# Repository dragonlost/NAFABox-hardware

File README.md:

# NAFABox-hardware   

__Version francaise :__    

Le but de ce projet, qui est née fin 2018, est de pouvoir proposer à tous des cartes électroniques plugables sur une carte Raspberry Pi (ou carte avec connecteur 40pins compatible) dédié aux astronomes amateurs.

Après 2 prototypes réalisés mais pas assez fonctionnel et compact à mon goût, l'idée fut de partir sur une achitecture modulaire stackable sur un Raspberry Pi.

Grâce à Kicad et ses possibilités 3D nous avons pu mener à bien ce projet.

Malheuresement, n'ayant pas de formation en électronique/design de PCB ou en réalisation mécanique, les réalisatons ne sont pas parfaite et ne respecte surement pas totalement les normes et caractéristique du domaine.

Ce projet est Open Source et donc j'invite toutes personnes voulant contribuer à sa réalisation à proposer un Pull Request/Issue ou à me contacter via mon Pseudo (le même que sur Github) sur Webastro ou sur le Discord : "Astro - FR".

__Attention :__ La plupart des modèles 3D présent dans de dossier __lib__ de chaque PCB sont issue du site https://grabcad.com/ et ne sont pas forcement tous OpenSource. Merci de respecter leurs droits de diffusion.

## Les différentes cartes :

Tout les schémas électronique sont disponible dans la Doc : https://github.com/dragonlost/NAFABox-hardware/tree/master/Doc/schema_pdf

### La carte de base :
(base_hat)     

Cette carte contient principalement 2 parties : 
- un composant DS3231 en I2C afin de pouvoir obtenir une base de temps permanente pour le Raspberry Pi ainsi qu'un logement de pile pour un CR2032 remplacable
- un connecteur et emplacement pour un ventillateur de 30x30mm controlé en PWM par le Raspberry PI.  

### La carte d'alimentation :
(alim_hat)    

Elle contient :
- Une entrée d'alimentation Jack DC protégé contre l'inversion de courant.
- 4 sorties :
	- protégées par des fusibles rearmable PPTC ( polyswitch/polyfuse) de 5A
	- mesurer en courant et tension à l'aide d'INA219 en I2C ( un par sortie)
	- de tension identique à la tension d'entrée
- un connecteur 8 broches avec la tension d'entré (x2) et la masse (x4) ainsi qu'une autre tension (VCC) entrée via le bornier prevue à cette effet
- un convertisseur DC-DC stepdown PDQE15-Q24-S5-D isolé ( désactivable) pouvant délivré 3A en 5V relié au pins 5v du Raspberry Pi.
- de pin permettant de couper/connecter chaque sortie via un Jumper ou des interupteurs externe ou via la carte relais.

### La carte Relais/ Focuser
(relais_hat)

Elle contient :
- Un système de 4 relais :
	- 4 relais piloté via les GPIO de carte Raspberry PI (GPIO 17, 18, 22 et 23)
	- 4 leds indiquant l'état des relais (dans le même ordre D1, D2, D3, D4)
	- 4 sorties par pins plugable sur la carte d'alimentation pour piloter les 4 sorties.
	- 4 bornier pour piloter un système externe
- un connecteur 8 broches avec la tension d'entrée (x2) et la masse (x4) ainsi qu'une autre tension (VCC) entrée via le bornier de la carte d'alimentation
- Un système pour piloter un moteur pas à pas afin de réaliser la mise au point.
	- un emplacemnt pour driveur moteur au format pololu
	- un connecteur DB9 au format RoboFocus (A1=1, A2=2, B1=3, B2=4, GND=5)
	- un système de 3 jumper afin de piloter l'état des pins (libre, 3.3v, GND)
	- pilotage via les GPIO (STEP=GPIO25, DIR=GPIO27, SLP=GPIO24)
	- l'alimentation 12v via la connecteur 8 pins.

### La carte Resistance chauffante et GPS
(res_hat)

Elle contient :
- un connecteur 8 broches avec la tension d'entrée (x2) et la masse (x4) ainsi qu'une autre tension (VCC) entrée via le bornier de la carte d'alimentation
- un connecteur 4 pins pour connecteur une carte GPS UART (3.3v-RX-TX-GND) :
	- 2 trous de fixation mécanique
	- 2 systèmes de jumper afin d'inverser le TX/RX ou sélectioner d'autre pin TX-RX pour la carte Nanopi-M4 
- une entrée Jack DC connecter a la tension VCC.
- un système de résistance chauffante piloter par I2C :
	- 2 résistance possible, connectable via 2x USB (résistance en 5V par exemple) ou via 2x RCA.
	- chaque sortie est mesurée en tension et courant via des INA219 comme la carte d'alimentation
	- un connecteur pour une carte BME280 en i2C afin de calculer le point de rosé via la température et l'humidité local.
	- 2 connecteurs pour 2 capteurs D18B20 1wire (pin7 du RPI) afin de mesurer la température des résistances.
	- Chaque résistance est pilotable en puissance via 2 mofset FDD844L-F085
	- Il est posible via un jumper de sélectionner la tension d'alimentation des résistances entre l'entrée Jack de la carte d'alimentation (nomé: 12V) et l'entrée jack de la carte résistance ou du bornier de la carte d'alimentation (nomé: VCC)

## Le Boitier :

Le boitier destiné à accueillir les différentes cartes a été concue comme les cartes afin d'être modulaire. Chaque carte possède donc sa propre pièce.    
Les modèles 3D des cartes sont aussi disponibles afin de permettre à chacun de réaliser son propre boitier.

Elle a été aussi concu afin d'être facilement imprimable sur des imprimantes de capacité d'impression de 20x20x20.    

Les pièces ont été dessiné sous CATIA par __SUPAII__ puis publié en format STEP afin que chacun puisse les modifiés/convertir avec n'importe quel logiciel de CAO.

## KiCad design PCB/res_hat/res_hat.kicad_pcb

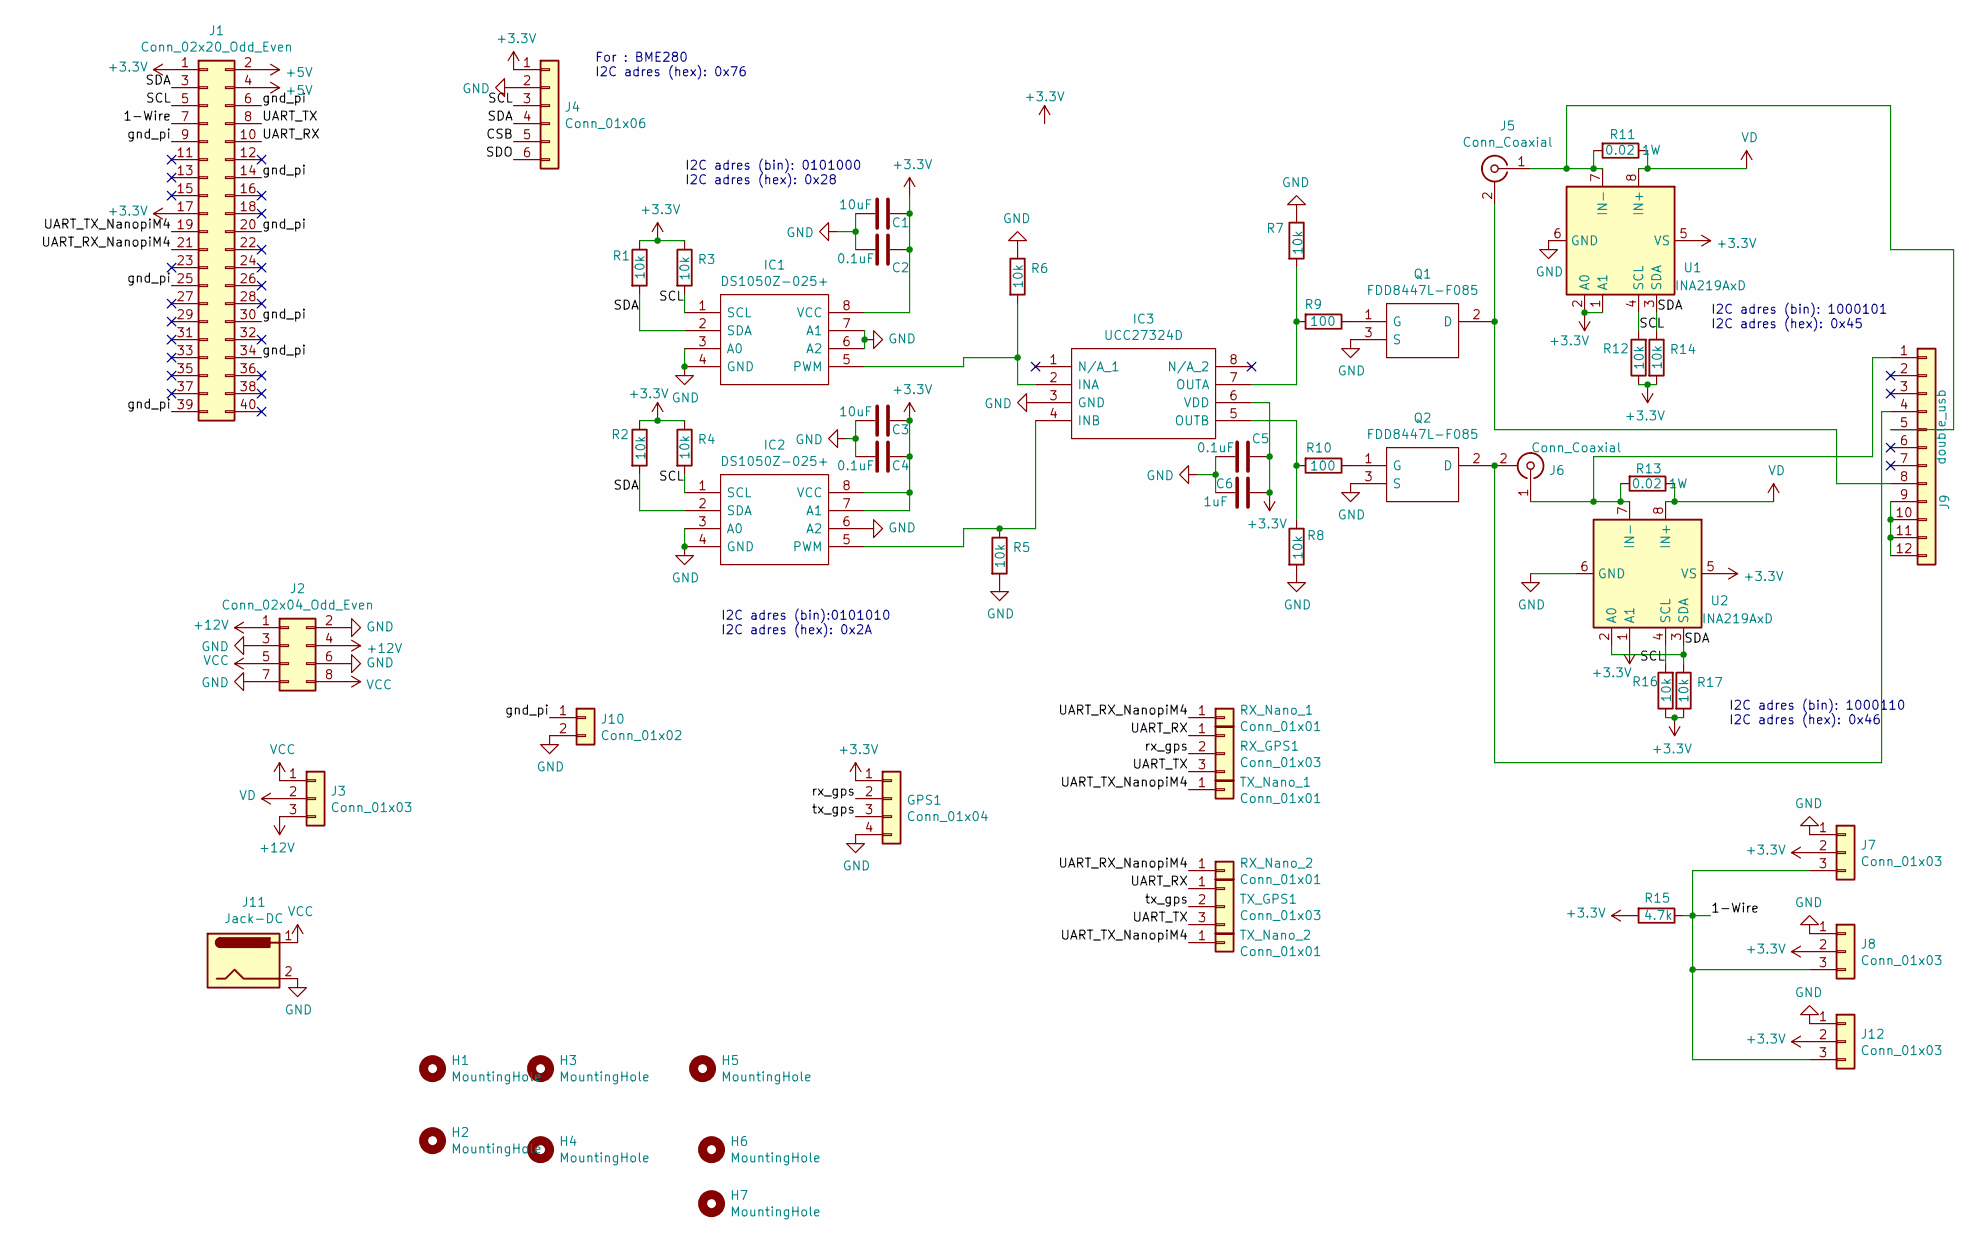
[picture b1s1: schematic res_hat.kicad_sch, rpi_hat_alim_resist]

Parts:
C1, C3: 10uF; C_0805_2012Metric; LCSC C15850
C2, C4, C5: 0.1uF; C_0805_2012Metric; LCSC C49678
C6: 1uF; C_0805_2012Metric; LCSC C28323
GPS1: Conn_01x04; PinSocket_1x04_P2.54mm_Vertical
H1, H2, H3, H4, H5, H6, H7: MountingHole; MountingHole_3.2mm_M3
IC1, IC2: DS1050Z-025+; SOIC127P600X175-8N; Mouser Part Number 700-DS1050Z-025
IC3: UCC27324D; SOIC127P600X175-8N; Mouser Part Number 595-UCC27324D
J1: Conn_02x20_Odd_Even; PinHeader_2x20_P2.54mm_Vertical
J2: Conn_02x04_Odd_Even; PinHeader_2x04_P2.54mm_Vertical
J3: Conn_01x03; PinHeader_1x03_P2.54mm_Vertical
J4: Conn_01x06; PinHeader_1x06_P2.54mm_Vertical
J5, J6: Conn_Coaxial; KLPX0848A2O
J7, J8, J12: Conn_01x03; Molex_KK-254_AE-6410-03A_1x03_P2.54mm_Vertical
J9: double_usb; DUAL_USB_2.0_TYPE-A
J10: Conn_01x02; PinHeader_1x02_P2.54mm_Vertical
J11: Jack-DC; BarrelJack_Horizontal
Q1, Q2: FDD8447L-F085; FDD8447LF085; Mouser Part Number 512-FDD8447L_F085
R1, R2, R3, R4, R5, R6, R7, R8, R12, R14, R16, R17: 10k; R_0805_2012Metric; LCSC C17414
R9: 100; R_0805_2012Metric; LCSC C17414
R10: 100; R_0805_2012Metric; LCSC C17408
R11, R13: 0.02 1W; R_2512_6332Metric; LCSC C127705
R15: 4.7k; R_0805_2012Metric; LCSC C17673
RX_GPS1: Conn_01x03; PinHeader_1x03_P2.54mm_Vertical
RX_Nano_1, RX_Nano_2: Conn_01x01; PinHeader_1x01_P2.54mm_Vertical
TX_GPS1: Conn_01x03; PinHeader_1x03_P2.54mm_Vertical
TX_Nano_1, TX_Nano_2: Conn_01x01; PinHeader_1x01_P2.54mm_Vertical
U1, U2: INA219AxD; SOIC-8_3.9x4.9mm_P1.27mm; LCSC C138706

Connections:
+5V: J1.2, J1.4
+12V: J2.1, J2.4, J3.3
/1-Wire: J1.7, J7.3, J8.3, J12.3, R15.1
/CSB: J4.5
/SCL: IC1.1 (SCL), IC2.1 (SCL), J1.5, J4.3, R3.2, R4.2, R12.2, R16.2, U1.4 (SCL), U2.4 (SCL)
/SDA: IC1.2 (SDA), IC2.2 (SDA), J1.3, J4.4, R1.2, R2.2, R14.1, R17.1, U1.3 (SDA), U2.2 (A0), U2.3 (SDA)
/SDO: J4.6
/UART_RX: J1.10, RX_GPS1.1, TX_GPS1.1
/UART_RX_NanopiM4: J1.21, RX_Nano_1.1, RX_Nano_2.1
/UART_TX: J1.8, RX_GPS1.3, TX_GPS1.3
/UART_TX_NanopiM4: J1.19, TX_Nano_1.1, TX_Nano_2.1
/gnd_pi: J1.6, J1.9, J1.14, J1.20, J1.25, J1.30, J1.34, J1.39, J10.1
/rx_gps: GPS1.2, RX_GPS1.2
/tx_gps: GPS1.3, TX_GPS1.2
GND: C1.1, C2.1, C3.1, C4.1, C5.2, C6.2, GPS1.4, IC1.3 (A0), IC1.4 (GND), IC1.6 (A2), IC1.7 (A1), IC2.3 (A0), IC2.4 (GND), IC2.6 (A2), IC3.3 (GND), J2.2, J2.3, J2.6, J2.7, J4.2, J7.1, J8.1, J10.2, J11.2, J12.1, Q1.3 (S), Q2.3 (S), R5.2, R6.1, R7.1, R8.2, U1.6 (GND), U2.6 (GND)
unnamed: IC1.5 (PWM), IC3.2 (INA), R6.2
unnamed: IC2.5 (PWM), IC3.4 (INB), R5.1
unnamed: IC3.7 (OUTA), R7.2, R9.2
unnamed: IC3.5 (OUTB), R8.1, R10.2
unnamed: J5.2 (Ext), J9.8, Q1.2 (D)
unnamed: J5.1 (In), J9.5, R11.2, U1.7 (IN-)
unnamed: J6.2 (Ext), J9.4, Q2.2 (D)
unnamed: J6.1 (In), J9.1, R13.2, U2.7 (IN-)
unnamed: J9.9, J9.10, J9.11, J9.12
unnamed: Q1.1 (G), R9.1
unnamed: Q2.1 (G), R10.1
VCC: J2.5, J2.8, J3.1, J11.1
VD: J3.2, R11.1, R13.1, U1.8 (IN+), U2.8 (IN+)

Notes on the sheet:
I2C adres (bin): 1000110 I2C adres (hex): 0x46
For : BME280 I2C adres (hex): 0x76
I2C adres (bin):0101010 I2C adres (hex): 0x2A
I2C adres (bin): 0101000 I2C adres (hex): 0x28
I2C adres (bin): 1000101 I2C adres (hex): 0x45

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
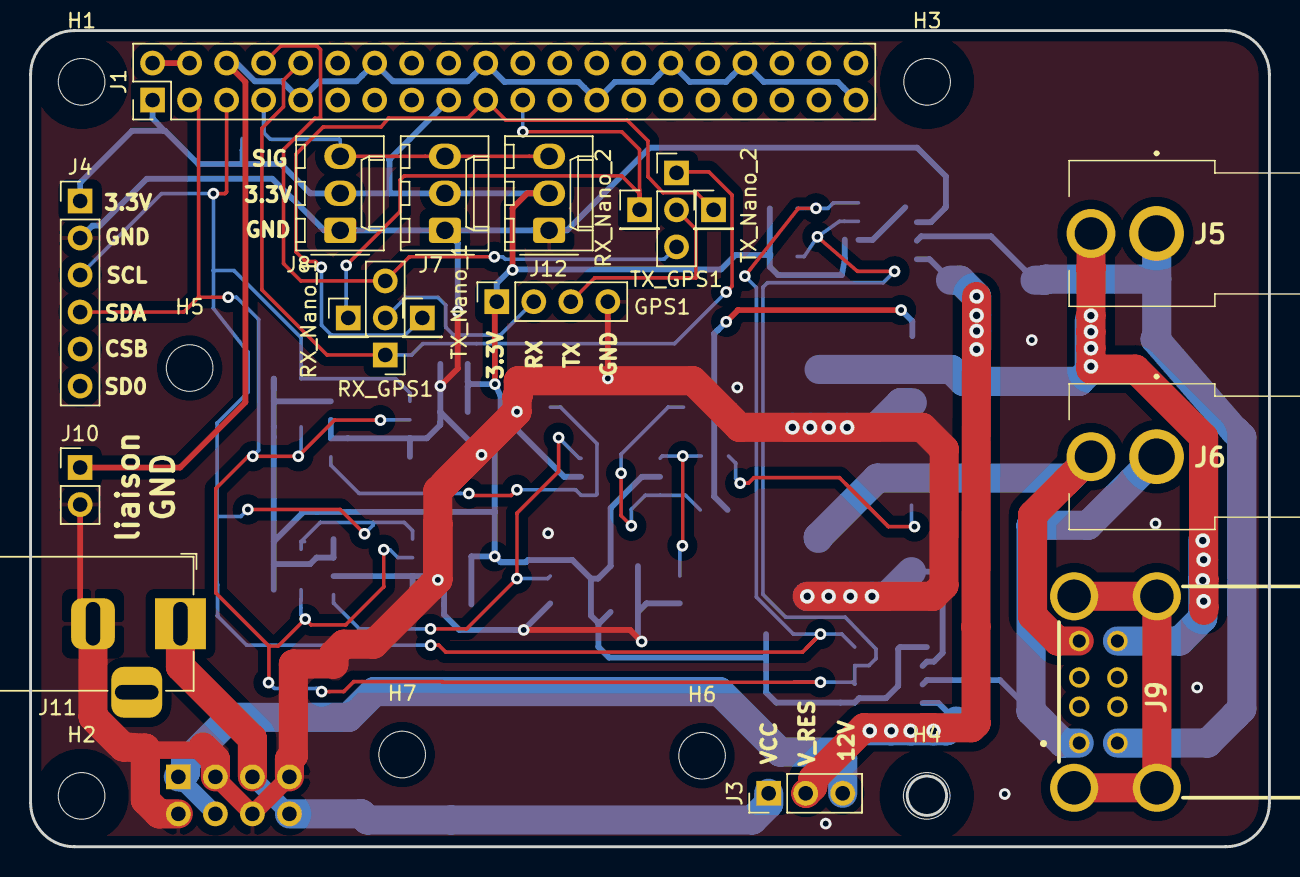
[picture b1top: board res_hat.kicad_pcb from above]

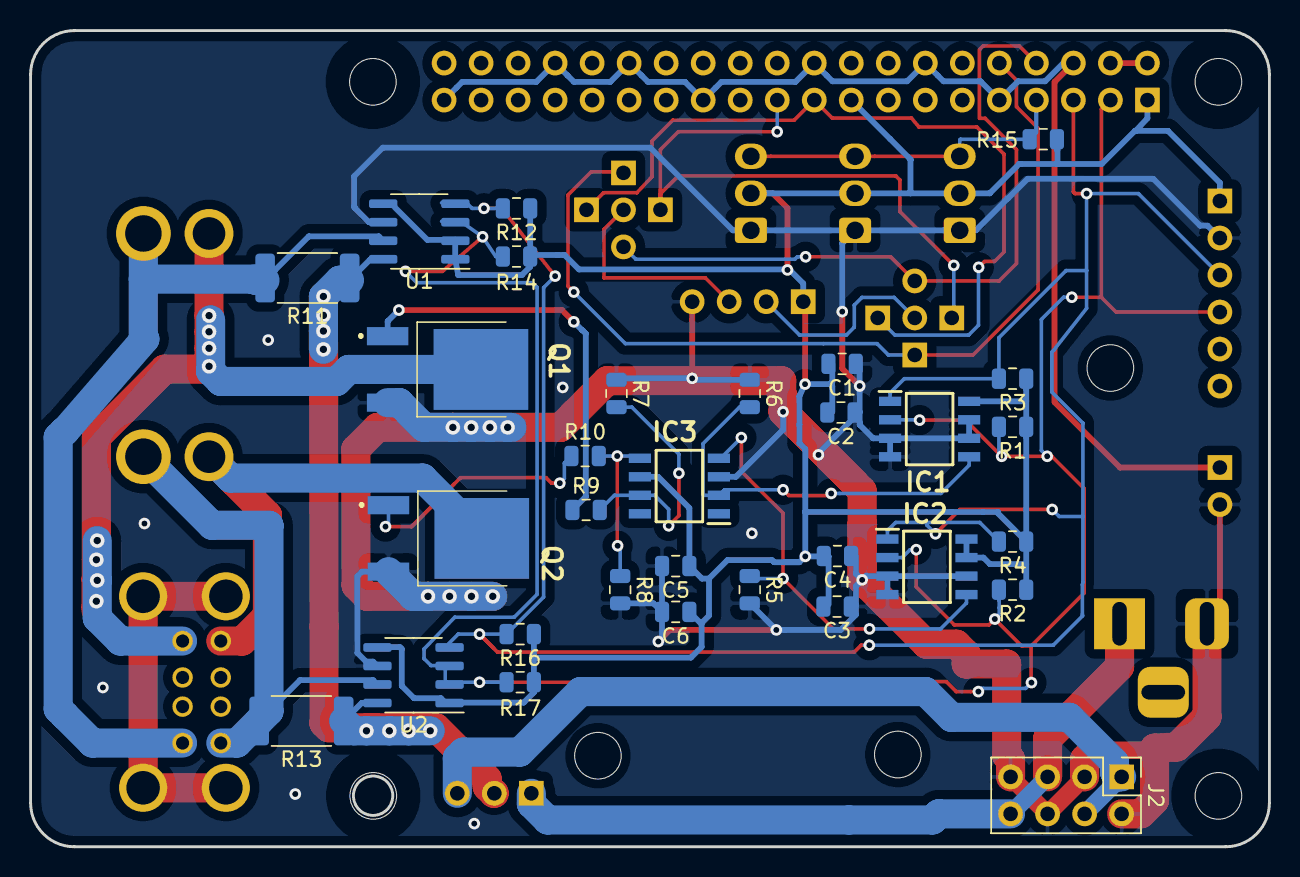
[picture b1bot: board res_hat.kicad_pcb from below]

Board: 2 copper layers, 85.0 x 56.0 mm, 56 parts (31 on the bottom side), 28 nets.

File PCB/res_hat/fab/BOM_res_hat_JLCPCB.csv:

Comment,Designator,Footprint,LCSC Part Number
10uF,"C1,C3",C_0805,C15850
0.1uF,"C2,C4,C5",C_0805,C49678
1uF,C6,C_0805,C28323
UCC27324D,IC3,SOIC-8,C46427
0.02 1W,"R11,R13",R_2512,C127705
4.7k,R15,R_0805,C17673
10k,"R1,R2,R3,R4,R5,R6,R7,R8,R12,R14,R16,R17",R_0805,C17414
100ohm,"R9,R10",R_0805,C17408
INA219AxD,"U1,U2",SOIC-8,C138706
MOSFET,"Q1,Q2",TO-252-2,C154314

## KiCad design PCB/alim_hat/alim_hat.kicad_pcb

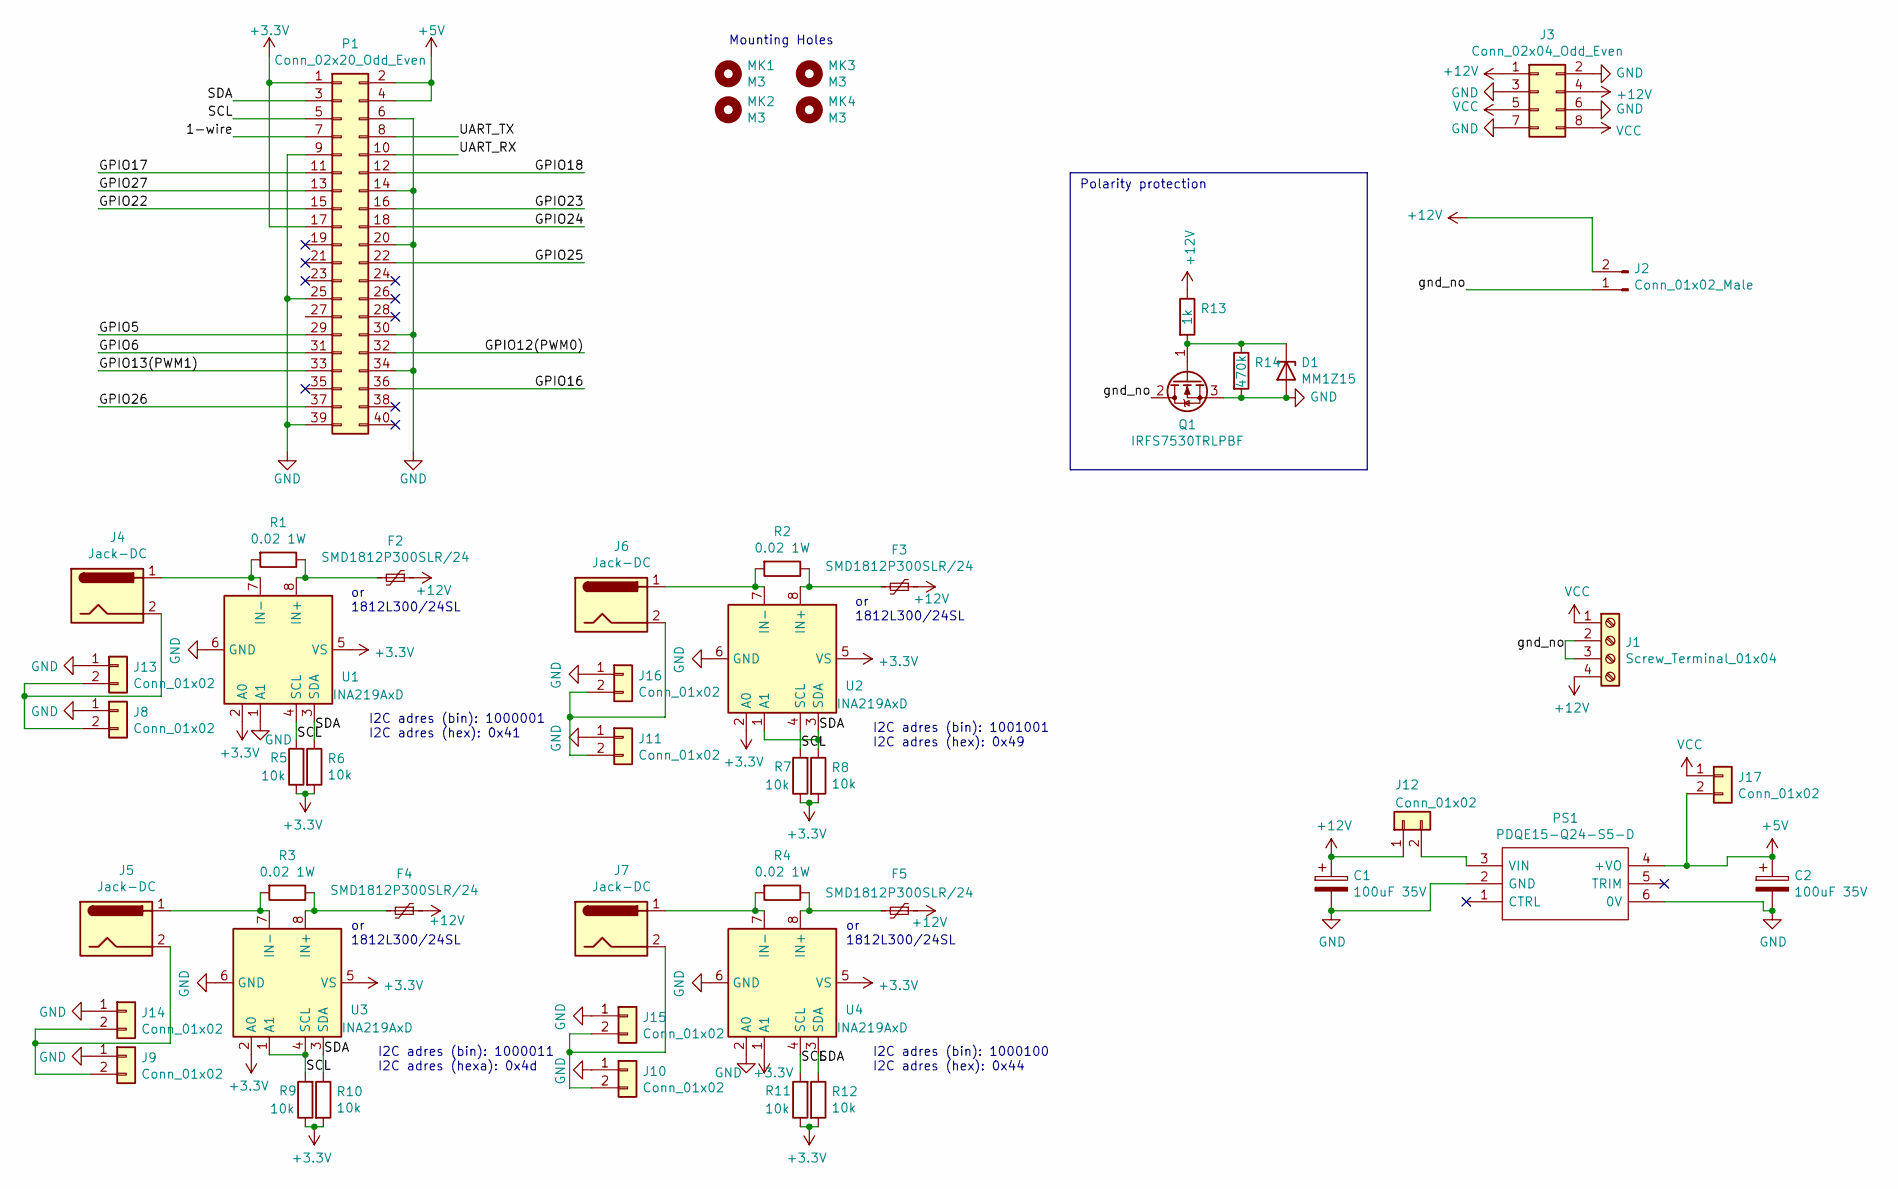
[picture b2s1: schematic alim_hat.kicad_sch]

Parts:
C1, C2: 100uF 35V; CP_Elec_6.3x7.7; LCSC C134792
D1: MM1Z15; D_SOD-123; LCSC C86235
F2, F3, F4: SMD1812P300SLR/24; Fuse_1812_4532Metric; LCSC C495359
F5: SMD1812P300SLR/24; Fuse_1812_4532Metric; LCSC SMD1812P300SLR/24
J1: Screw_Terminal_01x04; TerminalBlock_bornier-4_P5.08mm
J2: Conn_01x02_Male; AMASS_XT30PW-M_1x02_P2.50mm_Horizontal
J3: Conn_02x04_Odd_Even; PinHeader_2x04_P2.54mm_Vertical
J4, J5, J6, J7: Jack-DC; BarrelJack_Horizontal
J8, J9, J10, J11, J12, J13, J14, J15, J16, J17: Conn_01x02; PinHeader_1x02_P2.54mm_Vertical
MK1, MK2, MK3, MK4: M3; MountingHole_3.2mm_M3
P1: Conn_02x20_Odd_Even; PinSocket_2x20_P2.54mm_Vertical
PS1: PDQE15-Q24-S5-D; PDQE15Q24S5D; Manufacturer_Part_Number PDQE15-Q24-S5-D
Q1: IRFS7530TRLPBF; TO-263-2; LCSC C500544
R1, R2, R3, R4: 0.02 1W; R_2512_6332Metric; LCSC C127705
R5, R6, R7, R8, R9, R10, R11, R12: 10k; R_0805_2012Metric; LCSC C17414
R13: 1k; R_0805_2012Metric; LCSC C17513
R14: 470k; R_0805_2012Metric; LCSC C17709
U1, U2, U3, U4: INA219AxD; SOIC-8_3.9x4.9mm_P1.27mm; LCSC C138706

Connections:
+3.3V: P1.1, P1.17, R5.1, R6.2, R7.1, R8.2, R9.1, R10.2, R11.1, R12.2, U1.2 (A0), U1.5 (VS), U2.2 (A0), U2.5 (VS), U3.2 (A0), U3.5 (VS), U4.1 (A1), U4.5 (VS)
+5V: C2.1, J17.2, P1.2, P1.4, PS1.4 (+VO)
+12V: C1.1, F2.1, F3.1, F4.1, F5.1, J1.4, J2.2, J3.1, J3.4, J12.1, R13.1
/1-wire: P1.7
/GPIO5: P1.29
/GPIO6: P1.31
/GPIO12(PWM0): P1.32
/GPIO13(PWM1): P1.33
/GPIO16: P1.36
/GPIO17: P1.11
/GPIO18: P1.12
/GPIO22: P1.15
/GPIO23: P1.16
/GPIO24: P1.18
/GPIO25: P1.22
/GPIO26: P1.37
/GPIO27: P1.13
/SCL: P1.5, R5.2, R7.2, R9.2, R11.2, U1.4 (SCL), U2.4 (SCL), U3.1 (A1), U3.4 (SCL), U4.4 (SCL)
/SDA: P1.3, R6.1, R8.1, R10.1, R12.1, U1.3 (SDA), U2.1 (A1), U2.3 (SDA), U3.3 (SDA), U4.3 (SDA)
/UART_RX: P1.10
/UART_TX: P1.8
/gnd_no: J1.2, J1.3, J2.1, Q1.2 (D)
GND: C1.2, C2.2, D1.2 (A), J3.2, J3.3, J3.6, J3.7, J8.1, J9.1, J10.1, J11.1, J13.1, J14.1, J15.1, J16.1, P1.6, P1.9, P1.14, P1.20, P1.25, P1.30, P1.34, P1.39, PS1.2 (GND), PS1.6 (0V), Q1.3 (S), R14.2, U1.1 (A1), U1.6 (GND), U2.6 (GND), U3.6 (GND), U4.2 (A0), U4.6 (GND)
unnamed: D1.1 (K), Q1.1 (G), R13.2, R14.1
unnamed: J7.2, J10.2, J15.2
unnamed: J6.2, J11.2, J16.2
unnamed: J12.2, PS1.3 (VIN)
unnamed: J4.2, J8.2, J13.2
unnamed: J5.2, J9.2, J14.2
unnamed: F2.2, R1.1, U1.8 (IN+)
unnamed: J4.1, R1.2, U1.7 (IN-)
unnamed: F3.2, R2.1, U2.8 (IN+)
unnamed: J6.1, R2.2, U2.7 (IN-)
unnamed: F4.2, R3.1, U3.8 (IN+)
unnamed: J5.1, R3.2, U3.7 (IN-)
unnamed: F5.2, R4.1, U4.8 (IN+)
unnamed: J7.1, R4.2, U4.7 (IN-)
VCC: J1.1, J3.5, J3.8, J17.1

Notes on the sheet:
or 1812L300/24SL
I2C adres (bin): 1000100 I2C adres (hex): 0x44
Mounting Holes
I2C adres (bin): 1001001 I2C adres (hex): 0x49
I2C adres (bin): 1000001 I2C adres (hex): 0x41
Polarity protection
I2C adres (bin): 1000011 I2C adres (hexa): 0x4d

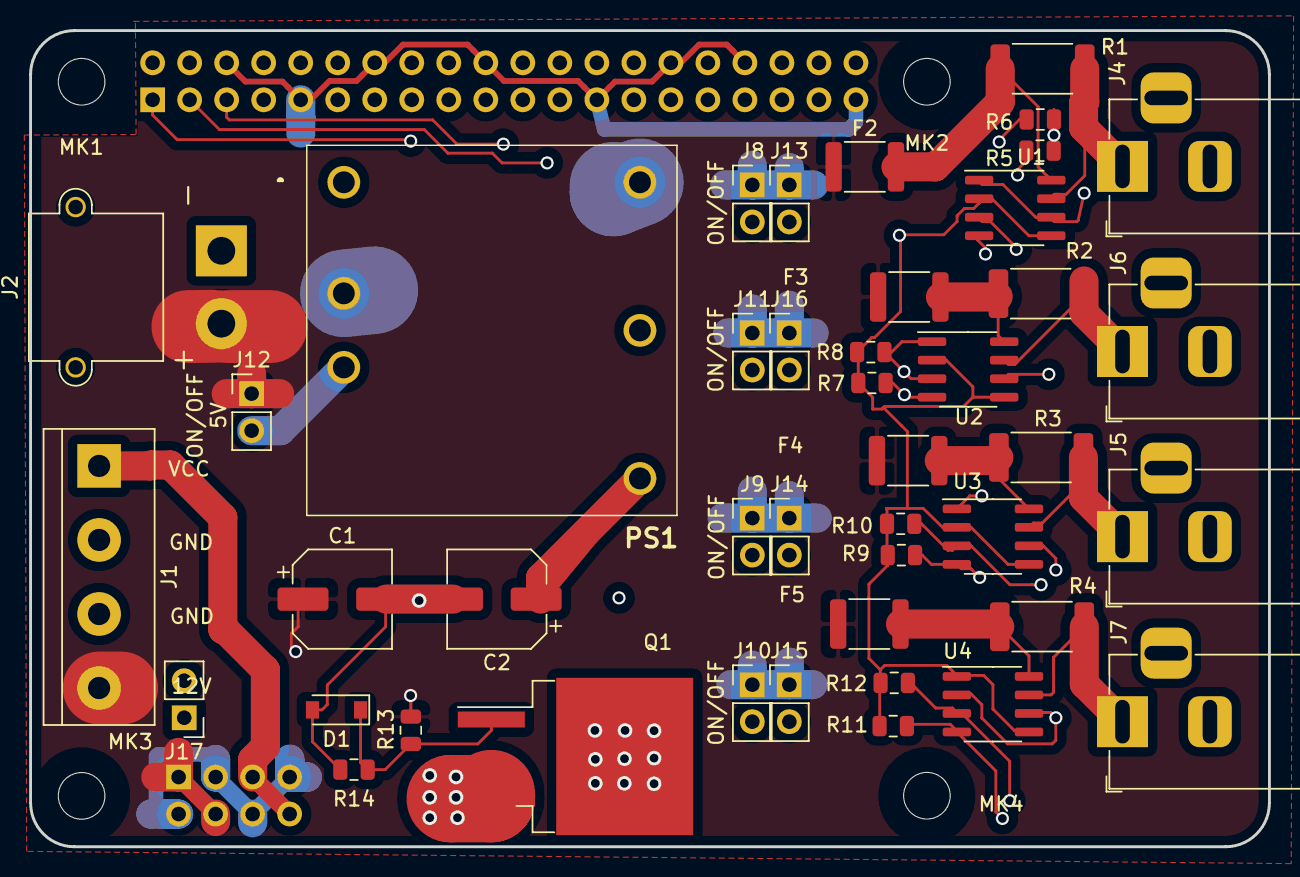
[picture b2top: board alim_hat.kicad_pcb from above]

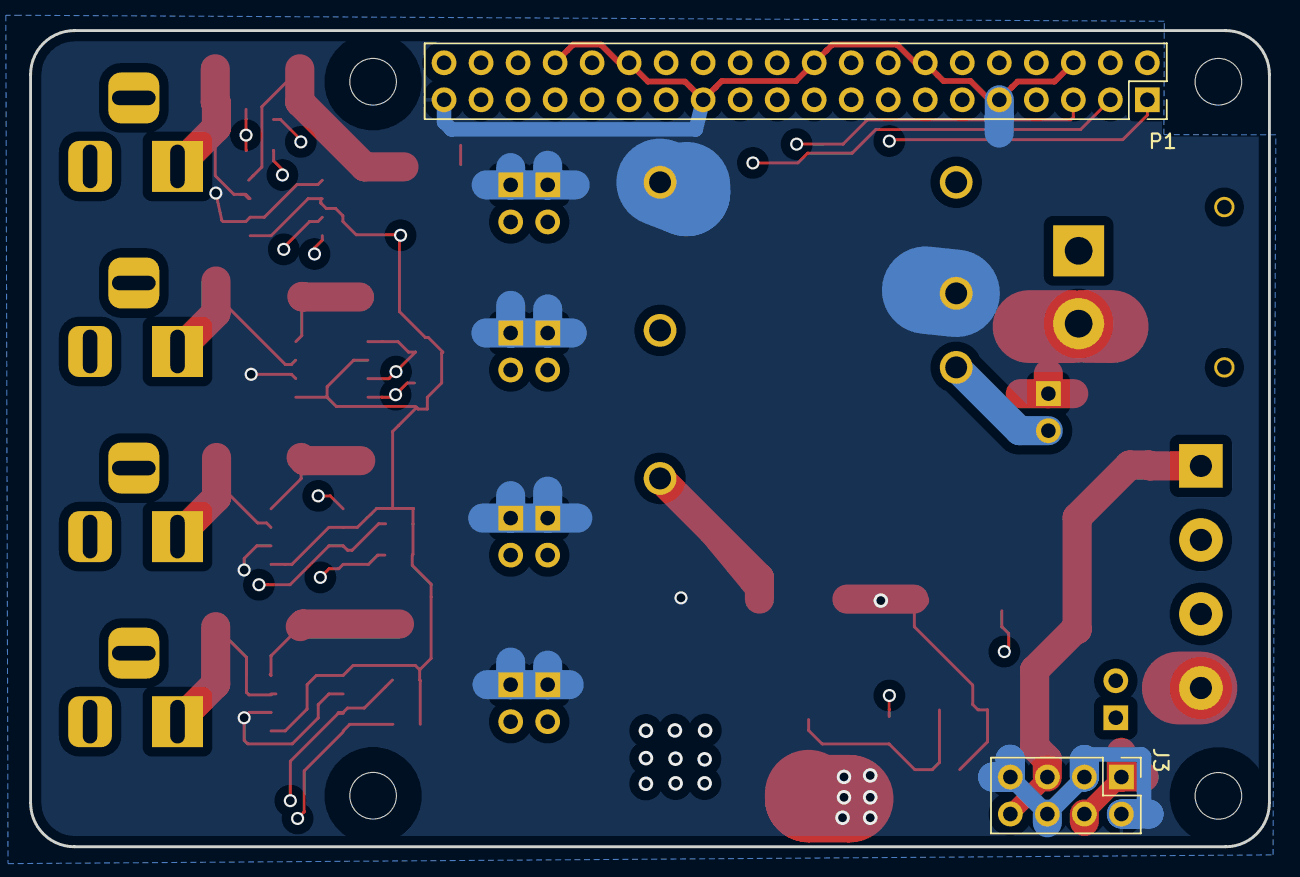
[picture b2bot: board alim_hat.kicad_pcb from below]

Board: 4 copper layers, 85.0 x 56.0 mm, 49 parts (2 on the bottom side), 22 nets.

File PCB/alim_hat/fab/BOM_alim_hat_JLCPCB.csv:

Comment,Designator,Footprint,LCSC Part Number
100uF,"C1,C2",CAPA 660X800,C134792
MM1Z15,D1,SOD-123,C86235
470k,R14,R 0805,C17709
1k,R13,R 0805,C17513
10k,"R5,R6,R7,R8,R9,R10,R11,R12",R 0805,C17414
INA219AxD,"U1,U2,U3,U4",SOIC-8,C138706
"0,02 1W","R1,R2,R3,R4",R 2512,C127705
IRFS7530,Q1,TO-263-2,C500544
SMD1812P300SLR/24,"F2,F3,F4,F5",Fuse 1812,C495359

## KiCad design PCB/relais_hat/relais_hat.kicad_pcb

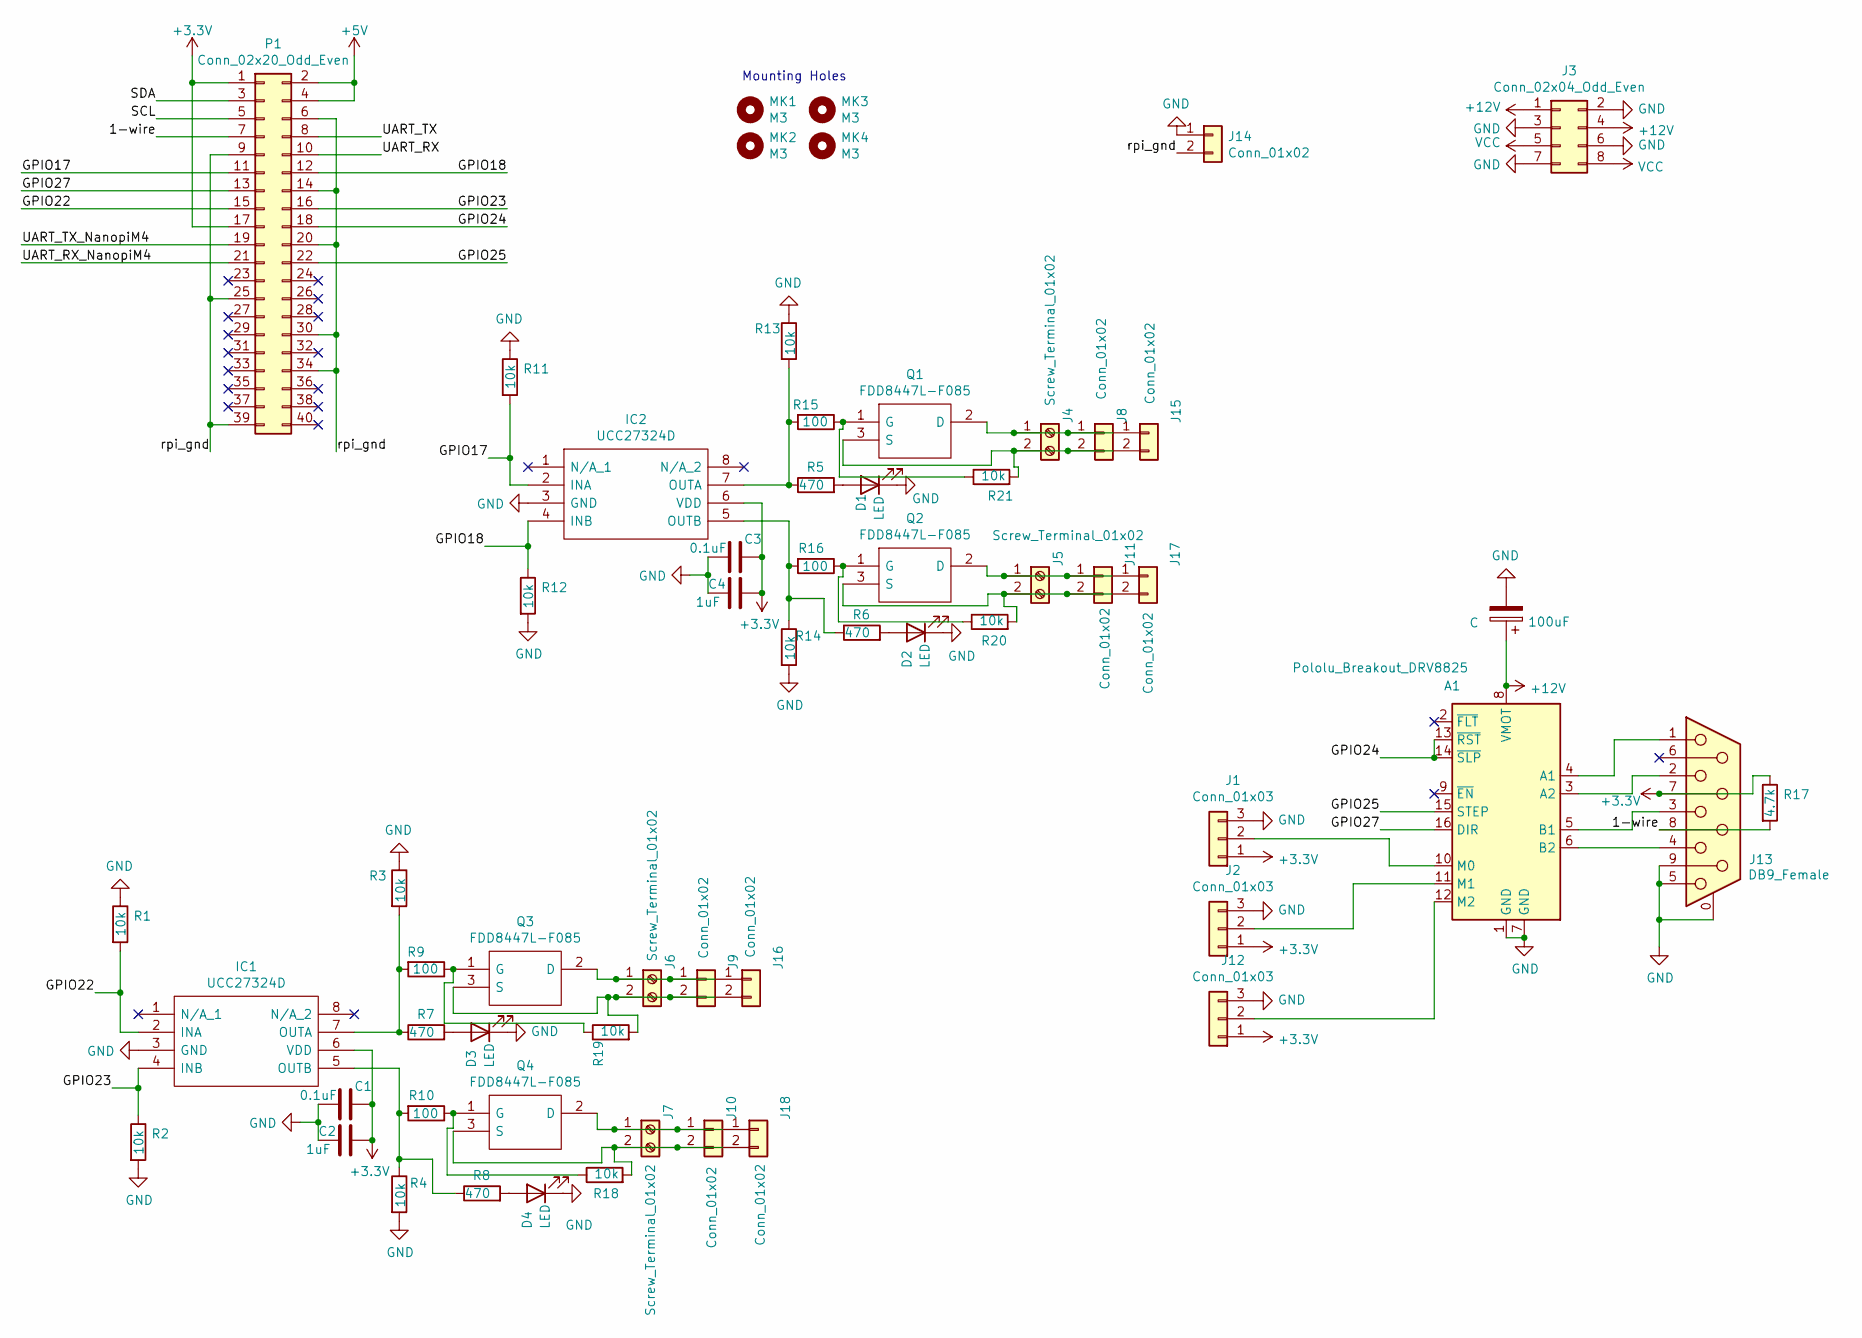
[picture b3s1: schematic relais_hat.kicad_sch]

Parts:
A1: Pololu_Breakout_DRV8825; Pololu_Breakout-16_15.2x20.3mm
C: 100uF; CP_Elec_6.3x7.7; LCSC C311622
C1, C3: 0.1uF; C_0805_2012Metric; LCSC C49678
C2, C4: 1uF; C_0805_2012Metric; LCSC C28323
D1, D2, D3, D4: LED; LED_0805_2012Metric; LCSC C84256
IC1, IC2: UCC27324D; SOIC127P600X175-8N; Mouser Part Number 595-UCC27324D
J1, J2, J12: Conn_01x03; PinHeader_1x03_P2.54mm_Vertical
J3: Conn_02x04_Odd_Even; PinHeader_2x04_P2.54mm_Vertical
J4, J5, J6, J7: Screw_Terminal_01x02; TerminalBlock_bornier-2_P5.08mm
J8, J9, J10, J11, J14, J15, J16, J17, J18: Conn_01x02; PinHeader_1x02_P2.54mm_Vertical
J13: DB9_Female; DSUB-9_Female_Horizontal_P2.77x2.84mm_EdgePinOffset4.94mm_H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
MK1, MK2, MK3, MK4: M3; MountingHole_2.7mm_M2.5
P1: Conn_02x20_Odd_Even; PinSocket_2x20_P2.54mm_Vertical
Q1, Q2, Q3, Q4: FDD8447L-F085; FDD8447LF085; Mouser Part Number 512-FDD8447L_F085
R1, R2, R3, R4, R11, R12, R13, R14, R18, R19, R20, R21: 10k; R_0805_2012Metric; LCSC C17414
R5, R6, R7, R8: 470; R_0805_2012Metric; LCSC C17710
R9, R15: 100; R_0805_2012Metric; LCSC C17414
R10, R16: 100; R_0805_2012Metric; LCSC C17408
R17: 4.7k; R_0805_2012Metric; LCSC C17673

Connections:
+3.3V: C1.1, C2.1, C3.1, C4.1, IC1.6 (VDD), IC2.6 (VDD), J1.1, J2.1, J12.1, J13.7, P1.1, P1.17, R17.1
+5V: P1.2, P1.4
+12V: A1.8 (VMOT), C.1, J3.1, J3.4
/1-wire: J13.8, P1.7, R17.2
/GPIO17: IC2.2 (INA), P1.11, R11.2
/GPIO18: IC2.4 (INB), P1.12, R12.1
/GPIO22: IC1.2 (INA), P1.15, R1.2
/GPIO23: IC1.4 (INB), P1.16, R2.1
/GPIO24: A1.13 (~RST), A1.14 (~SLP), P1.18
/GPIO25: A1.15 (STEP), P1.22
/GPIO27: A1.16 (DIR), P1.13
/SCL: P1.5
/SDA: P1.3
/UART_RX: P1.10
/UART_RX_NanopiM4: P1.21
/UART_TX: P1.8
/UART_TX_NanopiM4: P1.19
/rpi_gnd: J14.2, P1.6, P1.9, P1.14, P1.20, P1.25, P1.30, P1.34, P1.39
GND: A1.1 (GND), A1.7 (GND), C.2, C1.2, C2.2, C3.2, C4.2, D1.1 (K), D2.1 (K), D3.1 (K), D4.1 (K), IC1.3 (GND), IC2.3 (GND), J1.3, J2.3, J3.2, J3.3, J3.6, J3.7, J12.3, J13.0 (PAD), J13.5, J13.9, J14.1, R1.1, R2.2, R3.1, R4.2, R11.1, R12.2, R13.1, R14.2
unnamed: A1.4 (A1), J13.1
unnamed: A1.3 (A2), J13.2
unnamed: A1.5 (B1), J13.3
unnamed: A1.6 (B2), J13.4
unnamed: A1.10 (M0), J1.2
unnamed: A1.11 (M1), J2.2
unnamed: A1.12 (M2), J12.2
unnamed: D1.2 (A), R5.2
unnamed: D2.2 (A), R6.2
unnamed: D3.2 (A), R7.2
unnamed: D4.2 (A), R8.2
unnamed: IC1.7 (OUTA), R3.2, R7.1, R9.2
unnamed: IC1.5 (OUTB), R4.1, R8.1, R10.2
unnamed: IC2.7 (OUTA), R5.1, R13.2, R15.2
unnamed: IC2.5 (OUTB), R6.1, R14.1, R16.2
unnamed: J7.1, J10.1, J18.1, Q4.2 (D)
unnamed: J7.2, J10.2, J18.2, Q4.3 (S), R18.2
unnamed: J5.1, J11.1, J17.1, Q2.2 (D)
unnamed: J5.2, J11.2, J17.2, Q2.3 (S), R20.2
unnamed: J4.1, J8.1, J15.1, Q1.2 (D)
unnamed: J4.2, J8.2, J15.2, Q1.3 (S), R21.2
unnamed: J6.1, J9.1, J16.1, Q3.2 (D)
unnamed: J6.2, J9.2, J16.2, Q3.3 (S), R19.2
unnamed: Q1.1 (G), R15.1, R21.1
unnamed: Q2.1 (G), R16.1, R20.1
unnamed: Q3.1 (G), R9.1, R19.1
unnamed: Q4.1 (G), R10.1, R18.1
VCC: J3.5, J3.8

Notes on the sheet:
Mounting Holes

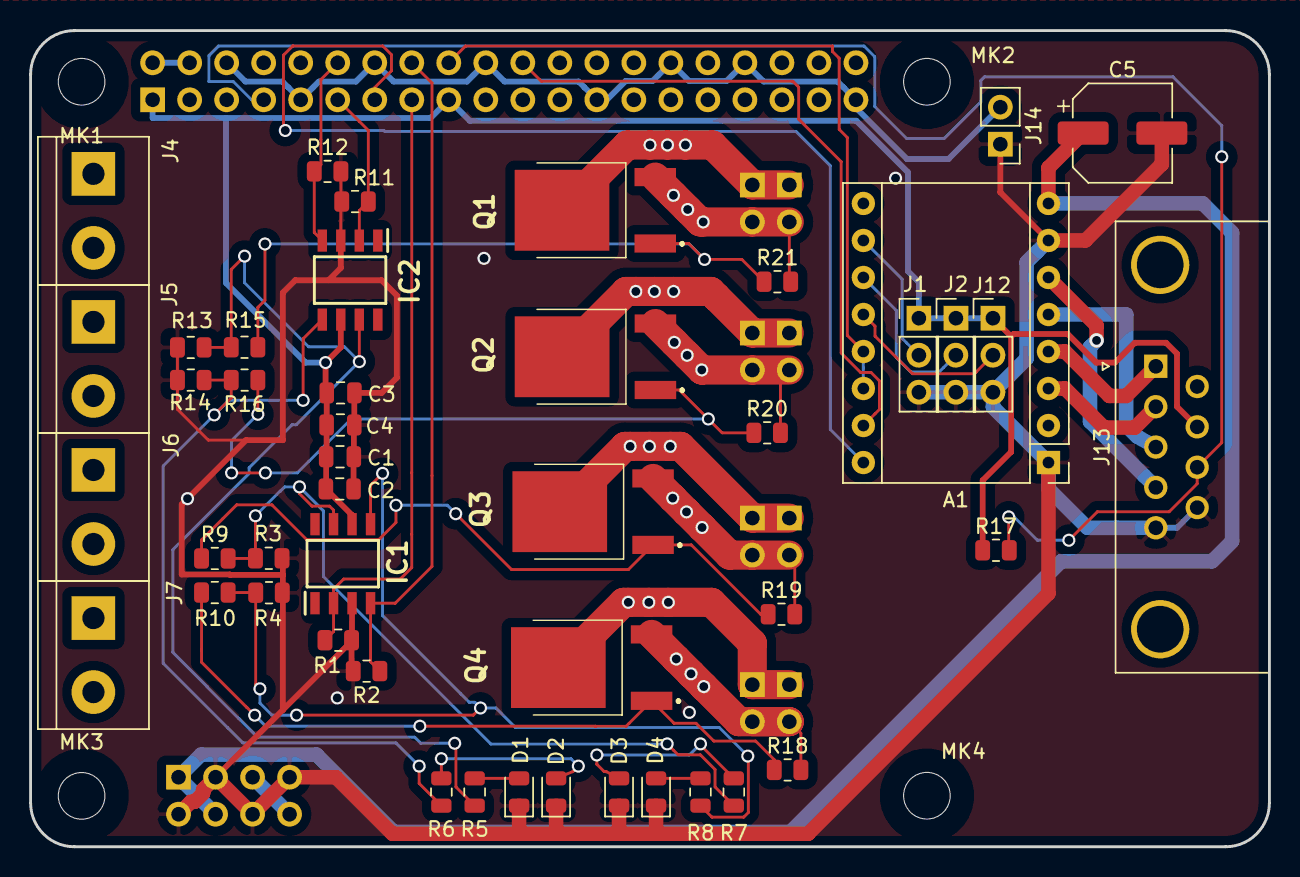
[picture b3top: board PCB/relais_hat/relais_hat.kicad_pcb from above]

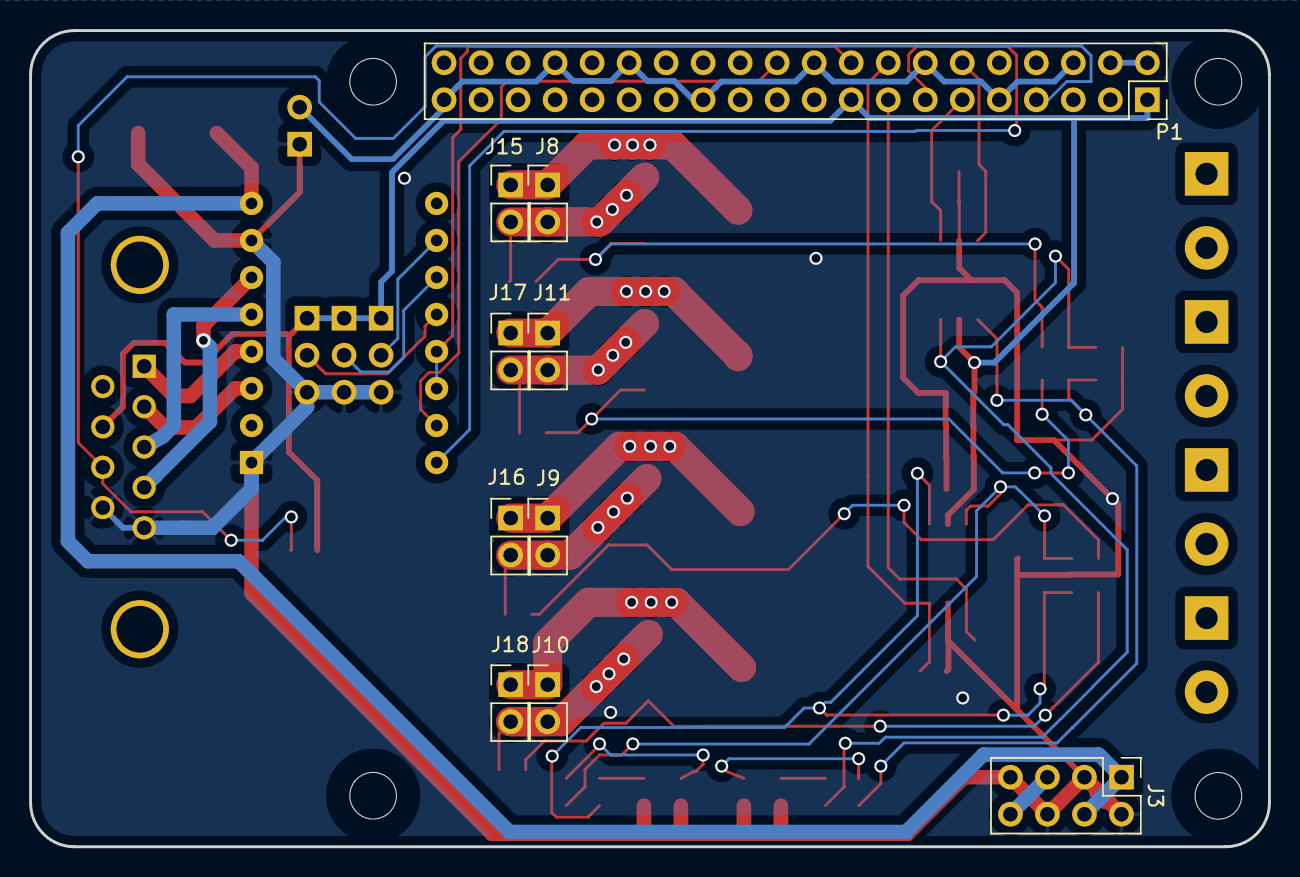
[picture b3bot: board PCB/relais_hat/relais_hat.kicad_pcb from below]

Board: 4 copper layers, 85.0 x 56.0 mm, 60 parts (10 on the bottom side), 41 nets.

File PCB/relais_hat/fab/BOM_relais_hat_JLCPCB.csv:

Comment,Designator,Footprint,LCSC Part Number
UCC27324D,"IC1, IC2, ",SOIC-8,C46427
100uF,C5,Cp 6.3x7.7,C134792
LED,"D1,D2,D3,D4",LED 0805,C84256
0.1uF,"C1, C3, ",C 0805,C49678
1uF,"C2, C4, ",C 0805,C28323
FDD8447L-F085,"Q1, Q2, Q3, Q4, ",TO-252-2,C154314
10k ohm,"R1, R2, R3, R4, R11, R12, R13, R14, R18, R19, R20, R21",R 0805,C17414
470 ohm,"R5,R6,R7,R8",R 0805,C17710
100 ohm,"R9, R10, R15, R16, ",R 0805,C17408
4.7k,R17,R_0805,C17673
